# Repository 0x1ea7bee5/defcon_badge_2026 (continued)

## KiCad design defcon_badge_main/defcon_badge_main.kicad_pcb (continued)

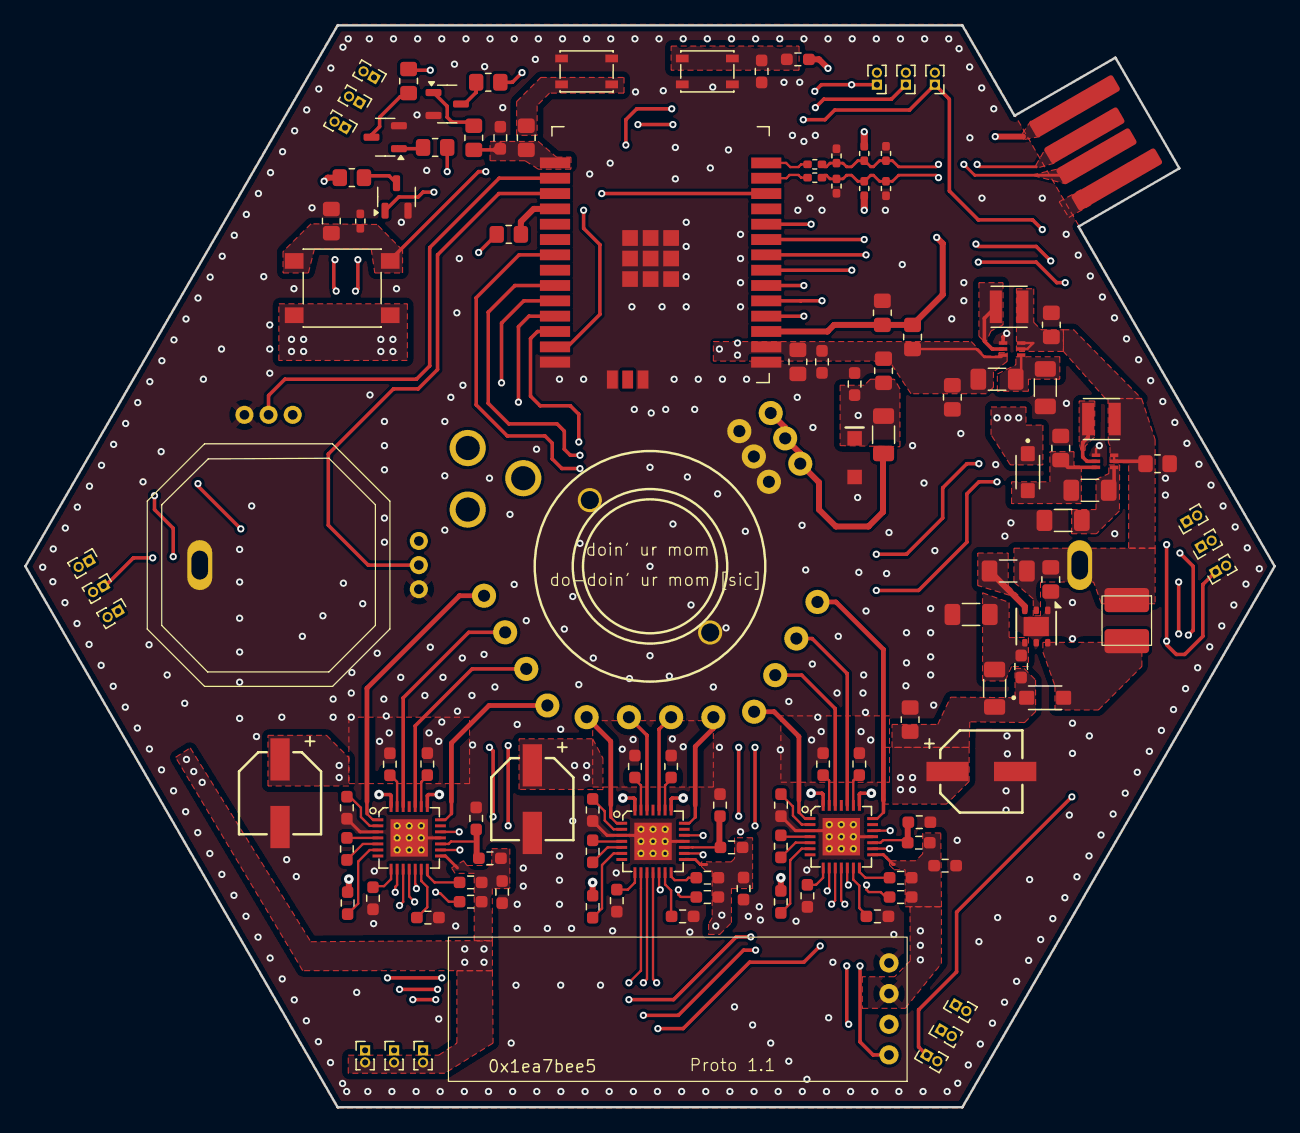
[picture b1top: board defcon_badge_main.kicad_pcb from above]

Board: 4 copper layers, 103.5 x 89.6 mm, 127 parts (1 on the bottom side), 93 nets.

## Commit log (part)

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2026-02-21 initial project
2026-02-22 progress from 2_21_26
2026-02-23 schematic complete
2026-02-23 Fixed footprint and naming issues
2026-02-24 ESP32 test board layout
2026-02-26 begin full layout
2026-03-02 more layout
2026-03-07 moar layout
2026-03-09 done?
2026-04-26 added component parts and modifications
2026-06-07 Started adding software
2026-06-08 Initial code added to wifi packet scanner. Additional unit tests added.
2026-06-09 now scrapes packets
2026-06-10 vibecoded V matrix creation and eigenvector decomposition
2026-06-14 moar code
2026-06-24 moar software changes
